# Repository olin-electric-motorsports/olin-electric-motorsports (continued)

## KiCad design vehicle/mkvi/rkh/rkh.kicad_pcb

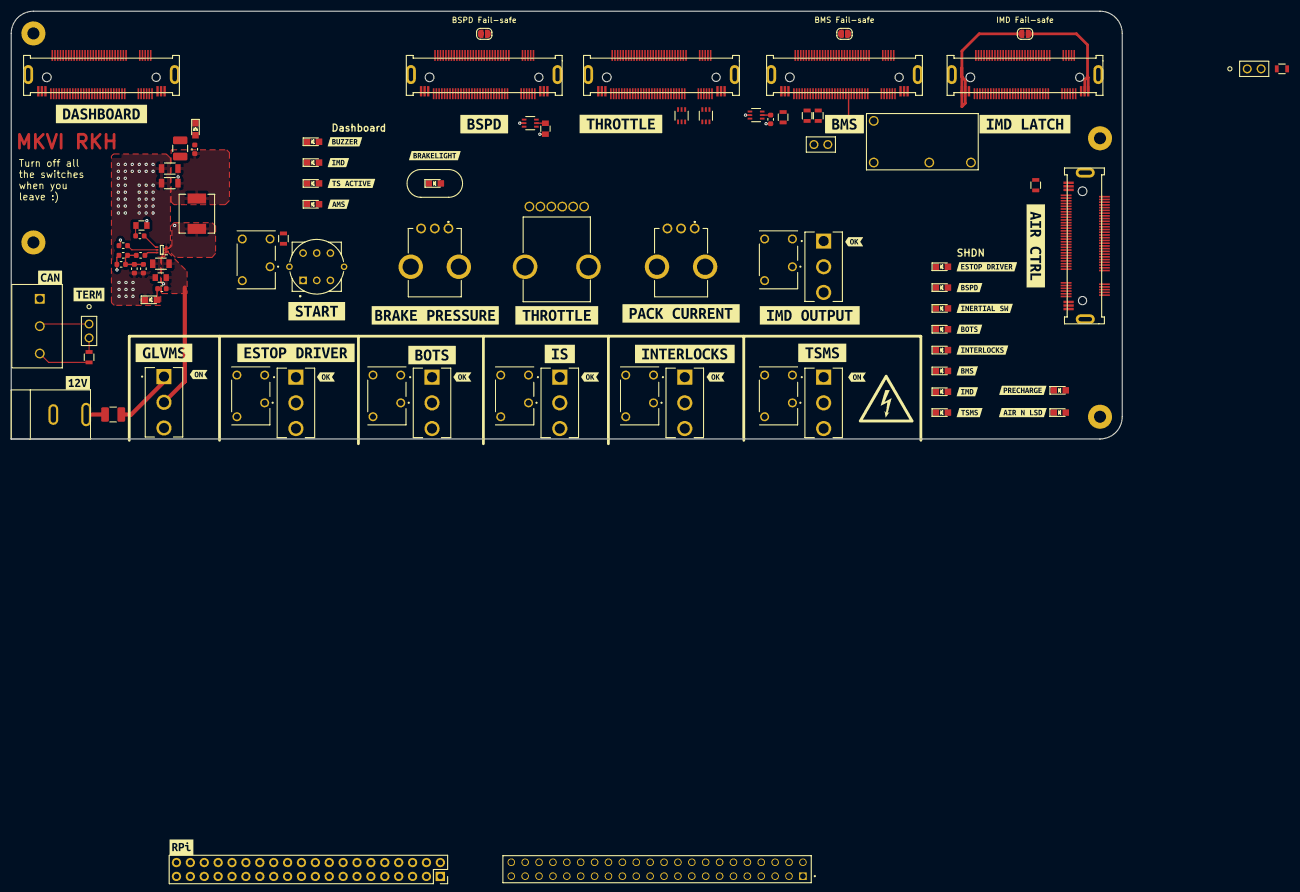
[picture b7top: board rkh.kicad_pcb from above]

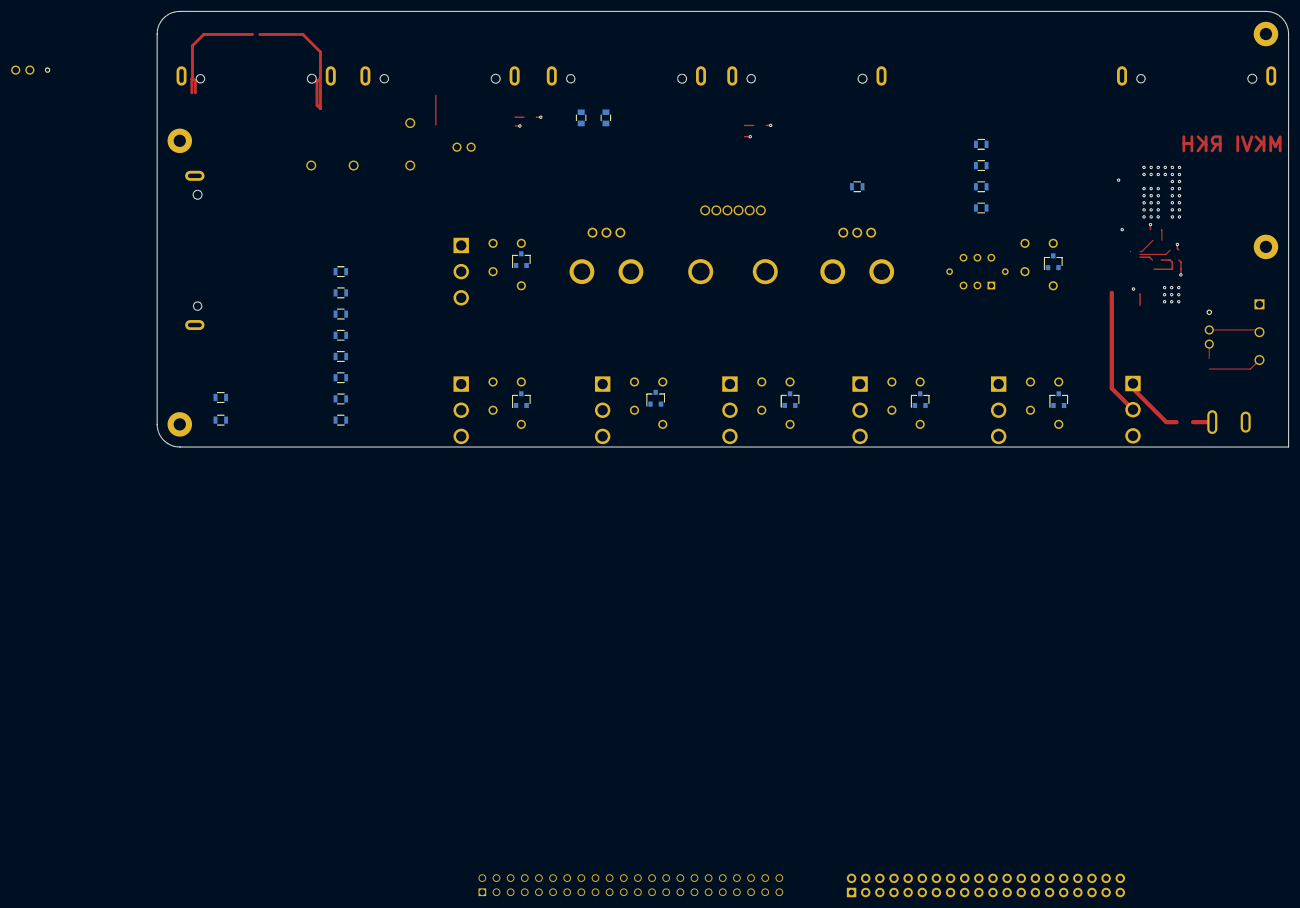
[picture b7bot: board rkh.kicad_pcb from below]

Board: 4 copper layers, 203.2 x 78.2 mm, 154 parts (24 on the bottom side), 90 nets.

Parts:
C601, C701, C702, C1003: C_1uF; C_0805_OEM
C1001: C_0.1uF; C_0805_OEM
C1002, C1005, C1006: C_22uF; C_1206_OEM
C1004: 15pF; C_0603_1608Metric
C1101: C_1uF; C_0603_1608Metric
D401, D402, D403, D404, D503, D504, D506, D507, D601, D801, D802, D804, D805, D901, D902, D1001, D1002: LED_0805; LED_0805_OEM
F201, F1001: Fuse; Fuse_1210_3225Metric_Pad1.42x2.65mm_HandSolder
H101, H102, H104, H105: MountingHole_Pad; MountingHole_2.2mm_M2_Pad
J101: Barrel_jack; barrel_jack_PJ-037A
J201: Screw_Terminal_01x03; ScrewPin_1x3
J202, J203, J1102: CONN_01x02; pinheader_1x2
J301: SSW-122-01-G-D; SAMTEC_SSW-122-01-G-D
J601, J701, J801, J1101, J1201, J1301: Automotive_M.2
J1202: Conn_02x20_Odd_Even; RaspberryPi_40pin_Connector
JP401, JP501, JP502: SolderJumper_2_Open; SolderJumper-2_P1.3mm_Open_RoundedPad1.0x1.5mm
K202, K401, K402, K403, K501, K801, K1201: G6L-1P_DC5; RELAY_G6L-1P_DC5
K1101: G5Q-1A4-DC5-5V; Relay_SPST_OMRON-G5Q-1A4_OEM
L1001: 2.2uH; IND_SPM6530T-2R2M
Q202, Q401, Q402, Q403, Q501, Q801, Q1201: SSM3K333R; SOT-23F
R201, R202: R_120; R_0805_OEM
R401, R402, R403, R404, R503, R504, R506, R507, R601, R801, R802, R803, R804, R903: R_1K; R_0805_OEM
R602, R901, R902, R1101, R1102: R_10K; R_0805_OEM
R805: R_100; R_0805_OEM
R1001: R_100K; R_0603_1608Metric
R1002: 10R; R_0603_1608Metric
R1003: R_75k; R_0603_1608Metric
R1004: R_10K; R_0603_1608Metric
R1005: R_33.2k; R_0603_1608Metric
R1006: 40.2K; R_0603_1608Metric
R1007, R1008: R_1K; R_0603_1608Metric
RV601, RV1201: R_Potentiometer; PTV09A4020FB103
RV701: R_Potentiometer_Dual; PTV1124420AA503
SW201, SW202, SW405, SW406, SW407, SW501, SW1201: SW_SPST; SW_100SP1T1B4M2QE
SW802: LP4OA1PBBTG; SW_LP4OA1PBBTG
U601, U701, U702, U1101: TMUX1247DCKR
U1001: MP1477HGTF-P; SOTFL50P160X60-6N
kibuzzard-63A8E52C: G***; kibuzzard-63A8E52C
kibuzzard-63A8E507: G***; kibuzzard-63A8E507
kibuzzard-63A8E517: G***; kibuzzard-63A8E517
kibuzzard-63A8FA7E: G***; kibuzzard-63A8FA7E
kibuzzard-63A8FCD9: G***; kibuzzard-63A8FCD9
kibuzzard-63A8FFD0: G***; kibuzzard-63A8FFD0
kibuzzard-63A76ADE, kibuzzard-63A76ADE#2: G***; kibuzzard-63A76ADE
kibuzzard-63A76B48: G***; kibuzzard-63A76B48
kibuzzard-63A76DD2: G***; kibuzzard-63A76DD2
kibuzzard-63A76DDE: G***; kibuzzard-63A76DDE
kibuzzard-63A76DE3: G***; kibuzzard-63A76DE3
kibuzzard-63A76DF6: G***; kibuzzard-63A76DF6
kibuzzard-63A76E2E: G***; kibuzzard-63A76E2E
kibuzzard-63A76E4B: G***; kibuzzard-63A76E4B
kibuzzard-63A76E44: G***; kibuzzard-63A76E44
kibuzzard-63A760DD: G***; kibuzzard-63A760DD
kibuzzard-63A765AA: G***; kibuzzard-63A765AA
kibuzzard-63A765EA: G***; kibuzzard-63A765EA
kibuzzard-63A766BF, kibuzzard-63A766BF#2, kibuzzard-63A766BF#3, kibuzzard-63A766BF#4, kibuzzard-63A766BF#5: G***; kibuzzard-63A766BF
kibuzzard-63A768D6: G***; kibuzzard-63A768D6
kibuzzard-63A770B9: G***; kibuzzard-63A770B9
kibuzzard-63A770D3: G***; kibuzzard-63A770D3
kibuzzard-63A772B0: G***; kibuzzard-63A772B0
kibuzzard-63A773EA: G***; kibuzzard-63A773EA
kibuzzard-63A774A3: G***; kibuzzard-63A774A3
kibuzzard-63A775AA: G***; kibuzzard-63A775AA
kibuzzard-63A775CB: G***; kibuzzard-63A775CB
kibuzzard-63A781BB: G***; kibuzzard-63A781BB
kibuzzard-63A7606C, kibuzzard-63A7606C#2: G***; kibuzzard-63A7606C
kibuzzard-63A7727D: G***; kibuzzard-63A7727D
kibuzzard-63A7729E: G***; kibuzzard-63A7729E
kibuzzard-63A76058: G***; kibuzzard-63A76058
kibuzzard-63A76624: G***; kibuzzard-63A76624
kibuzzard-63A77227: G***; kibuzzard-63A77227
kibuzzard-63A77408: G***; kibuzzard-63A77408
kibuzzard-63A77485: G***; kibuzzard-63A77485
kibuzzard-63B35C4A: G***; kibuzzard-63B35C4A

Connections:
+5V: C601.2, C701.1, C702.1, C1101.2, F1001.2, J601.P1, J601.P2, J601.P3, J701.P38, J701.P39, J701.P40, J1101.P38, J1201.P1, J1202.2, J1202.4, J1301.P38, K202.8, K401.8, K402.8, K403.8, K501.8, K801.8, K1201.8, R602.1, R901.1, R902.1, R1101.1, RV601.1, RV701.1, RV701.4, RV1201.1, U601.2 (VDD), U701.2 (VDD), U702.2 (VDD), U1101.2 (VDD)
+12V: C1001.1, C1002.1, J301.42, J1301.P3, K401.4, K1101.1, K1201.4, R601.1, R801.1, R802.1, R803.1, R804.1, R1001.1, R1007.1, SW201.2 (B), SW405.1 (A), SW1201.1 (A), U1001.1 (VIN)
/Buck Converter/BUCK_EN: R1001.2, U1001.5 (EN)
/Hardware in the Loop/CAN.N: J201.3, J301.44, J601.8, J701.8, J801.7, J1101.8, J1201.15, R201.2, R202.2
/Hardware in the Loop/CAN.P: J201.2, J202.1, J203.1, J301.43, J601.7, J701.7, J801.8, J1101.7, J1201.14
/Hardware in the Loop/HITL_DAC1: J301.27, U701.1 (S2)
/Hardware in the Loop/HITL_DAC2: J301.28, U702.1 (S2)
/Hardware in the Loop/HITL_DAC3: J301.29, U601.1 (S2)
/Hardware in the Loop/HITL_DAC4: J301.30, U1101.1 (S2)
/Hardware in the Loop/HITL_GPIO4: J301.12, U601.6 (SEL)
/Hardware in the Loop/HITL_GPIO5: J301.14, U702.6 (SEL)
/Hardware in the Loop/HITL_GPIO6: J301.16, U701.6 (SEL)
/Hardware in the Loop/HITL_GPIO7: J301.18, Q801.1 (G)
/Hardware in the Loop/HITL_GPIO9: J301.04, Q402.1 (G)
/Hardware in the Loop/HITL_GPIO10: J301.06, Q403.1 (G)
/Hardware in the Loop/HITL_GPIO12: D901.1 (K), J1101.24, J1101.25, R901.2
/Hardware in the Loop/HITL_GPIO13: J301.03, Q1201.1 (G)
/Hardware in the Loop/HITL_GPIO14: J301.05, Q501.1 (G)
/Hardware in the Loop/HITL_GPIO15: J301.07, J1101.13, J1301.33
/Hardware in the Loop/HITL_GPIO16: J301.10, J1101.30, R903.1
/Hardware in the Loop/HITL_GPIO17: J301.09, J1101.27
/MSB/GLV_BATT+: F201.1, J101.1 (center)
/Nostril/BSPD/BRAKELIGHT_LOW_SIDE: D601.1 (K), J601.14, J601.15, R602.2
/Nostril/BSPD/BRAKE_PRESSURE_POT: RV601.2, U601.3 (S1)
/Nostril/BSPD/BRAKE_PRESSURE_SENSE: J601.11, U601.4 (D)
/Nostril/BSPD/SHDN_FROM_BSPD: J601.22, J601.23, JP401.2 (B), K402.4, SW406.1 (A)
/Nostril/BSPD_I_SENSE: J601.12, J1201.18
/Nostril/Dashboard/BMS_LED_LSD: D801.1 (K), J801.12
/Nostril/Dashboard/BUZZER_LSD: D805.1 (K), J801.13
/Nostril/Dashboard/IMD_LED_LSD: D802.1 (K), J801.10
/Nostril/Dashboard/START_BTN_A: J801.34, K801.4, SW802.4, SW802.5
/Nostril/Dashboard/START_BTN_B: J801.35, K801.2, SW802.1, SW802.2
/Nostril/Dashboard/START_BTN_LED_+: J801.36, R805.2
/Nostril/Dashboard/START_BTN_LED_-: J801.37, SW802.L2
/Nostril/Dashboard/TS_LED_LSD: D804.1 (K), J801.15
/Nostril/SHDN_SENSE_BOTS: D404.2 (A), J801.18, K402.2, K403.4, SW406.2 (B), SW407.1 (A)
/Nostril/SHDN_SENSE_BSPD: D402.2 (A), J601.17
/Nostril/SHDN_SENSE_ESTOP_DRIVER: D401.2 (A), J601.19, J601.20, J801.17, JP401.1 (A), K401.2, SW405.2 (B)
/Nostril/SHDN_SENSE_IS: D403.2 (A), J701.12, K403.2, K501.4, SW407.2 (B), SW501.1 (A)
/Nostril/Throttle/APPS_POTENTIOMETER_A: RV701.2, U702.3 (S1)
/Nostril/Throttle/APPS_POTENTIOMETER_B: RV701.5, U701.3 (S1)
/Nostril/Throttle/THROTTLE_A_SENSE: J701.10, U702.4 (D)
/Nostril/Throttle/THROTTLE_B_SENSE: J701.5, U701.4 (D)
/Service Section/BMS Core/BMS_RELAY_LSD: J1201.17, K1101.5
/Service Section/BMS Core/CHARGE_ENABLE_IN: J1102.1, J1201.11
/Service Section/BMS Core/CHARGE_ENABLE_OUT: J1102.2, J1201.12
/Service Section/BMS Core/I_SENSE_VOUT: J1201.23, U1101.4 (D)
/Service Section/BMS Core/I_SENSE_VREF: J1201.24, R1101.2, R1102.1
/Service Section/BMS Core/PACK_I_SENSE_POT: RV1201.2, U1101.3 (S1)
/Service Section/IMD Latch/IMD_OUTPUT: J1301.34, K1201.2, SW1201.2 (B)
/Service Section/SHDN_SENSE_BMS: D504.2 (A), J1101.19, J1301.P1, J1301.P2, JP501.2 (B), JP502.1 (A), K1101.3
/Service Section/SHDN_SENSE_IMD: D506.2 (A), J1101.21, J1301.P39, J1301.P40, JP502.2 (B), K202.4, SW202.1 (A)
/Service Section/SHDN_SENSE_INTERLOCKS: D503.2 (A), J1101.15, J1101.16, J1101.18, JP501.1 (A), K501.2, K1101.2, SW501.2 (B)
/Service Section/SHDN_SENSE_TSMS: D507.2 (A), J1101.22, K202.2, SW202.2 (B)
GND: C601.1, C701.2, C702.2, C1001.2, C1002.2, C1005.2, C1006.2, C1101.1, D902.1 (K), D1001.1 (K), D1002.1 (K), H101.1, H102.1, H104.1, H105.1, J101.2 (Shell), J201.1, J301.01, J301.02, J301.25, J301.26, J301.41, J601.6, J601.9, J601.10, J601.13, J601.16, J601.18, J601.21, J601.24, J601.P38, J601.P39, J601.P40, J701.4, J701.6, J701.9, J701.11, J701.13, J801.6, J801.9, J801.11, J801.14, J801.16, J801.19, J801.P38, J801.P39, J801.P40, J1101.6, J1101.9, J1101.11, J1101.14, J1101.17, J1101.20, J1101.23, J1101.26, J1101.29, J1101.32, J1101.35, J1201.4, J1201.6, J1201.9, J1201.10, J1201.13, J1201.16, J1201.19, J1201.22, J1201.25, J1202.6, J1202.9, J1202.14, J1202.20, J1202.25, J1202.30, J1202.34, J1202.39, J1301.32, J1301.35, Q202.2 (S), Q401.2 (S), Q402.2 (S), Q403.2 (S), Q501.2 (S), Q801.2 (S), Q1201.2 (S), R401.2, R402.2, R403.2, R404.2, R503.2, R504.2, R506.2, R507.2, R1004.2, R1005.2, R1102.2, RV601.3, RV701.3, RV701.6, RV1201.3, U601.5 (GND), U701.5 (GND), U702.5 (GND), U1001.3 (GND), U1101.5 (GND)
unnamed: C1003.1, R1002.2
unnamed: C1003.2, L1001.1, U1001.2 (SW)
unnamed: C1004.1, R1003.2, R1004.1, R1005.1, R1006.1
unnamed: C1004.2, C1005.1, C1006.1, F1001.1, L1001.2, R1006.2, R1008.1
unnamed: D401.1 (K), R401.1
unnamed: D402.1 (K), R402.1
unnamed: D403.1 (K), R403.1
unnamed: D404.1 (K), R404.1
unnamed: D503.1 (K), R503.1
unnamed: D504.1 (K), R504.1
unnamed: D506.1 (K), R506.1
unnamed: D507.1 (K), R507.1
unnamed: D601.2 (A), R601.2
unnamed: D801.2 (A), R801.2
unnamed: D802.2 (A), R802.2
unnamed: D804.2 (A), R803.2
unnamed: D805.2 (A), R804.2
unnamed: D901.2 (A), R902.2
unnamed: D902.2 (A), R903.2
unnamed: D1001.2 (A), R1007.2
unnamed: D1002.2 (A), R1008.2
unnamed: F201.2, SW201.1 (A)
unnamed: J202.2, R201.1
unnamed: J203.2, R202.1
unnamed: J801.P1, J801.P2, J801.P3
unnamed: K202.5, Q202.3 (D)
unnamed: K401.5, Q401.3 (D)
unnamed: K402.5, Q402.3 (D)
unnamed: K403.5, Q403.3 (D)
unnamed: K501.5, Q501.3 (D)
unnamed: K801.5, Q801.3 (D)
unnamed: K1201.5, Q1201.3 (D)
unnamed: R805.1, SW802.L1
unnamed: R1002.1, U1001.4 (BST)
unnamed: R1003.1, U1001.6 (FB)

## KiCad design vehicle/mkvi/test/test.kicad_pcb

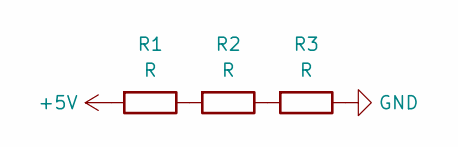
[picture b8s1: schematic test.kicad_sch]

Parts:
R1, R2, R3: R; R_0603_1608Metric

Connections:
+5V: R1.2
GND: R3.1
unnamed: R1.1, R2.2
unnamed: R2.1, R3.2

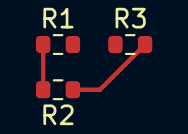
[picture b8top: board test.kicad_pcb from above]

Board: 2 copper layers, 3 parts (0 on the bottom side), 2 nets.
